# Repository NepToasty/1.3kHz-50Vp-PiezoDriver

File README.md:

# 1.3kHz-50Vp-PiezoDriver
1.3kHz 50Vp PiezoDriver

## Safety Warning and Disclaimer

This project is an experimental open-source hardware design. It can generate and/or expose voltages greater than 30 VAC, including potentially hazardous voltages. Contact with energized parts may cause electric shock, burns, equipment damage, fire, injury, or death.

This design is provided for informational, educational, and experimental use only. It is not a certified product, not safety-approved, and not intended for use in medical, life-support, safety-critical, automotive, industrial control, or other applications where failure could cause injury, death, property damage, or regulatory non-compliance.

Anyone who builds, modifies, tests, powers, or uses this design does so entirely at their own risk. The user is solely responsible for verifying the design, selecting suitable components, following applicable electrical safety practices, using appropriate insulation, fusing, enclosures, creepage/clearance distances, personal protective equipment, and complying with all applicable laws, standards, and regulations.

The authors, contributors, and copyright holders make no warranties or guarantees of any kind, express or implied, including but not limited to correctness, safety, fitness for a particular purpose, reliability, regulatory compliance, or suitability for any application.

To the fullest extent permitted by law, the authors, contributors, and copyright holders shall not be liable for any claim, damage, injury, loss, expense, or other liability arising from or related to the use, misuse, construction, modification, testing, or distribution of this project or any device based on it.

Do not build or operate this project unless you understand the risks of working with hazardous voltages.

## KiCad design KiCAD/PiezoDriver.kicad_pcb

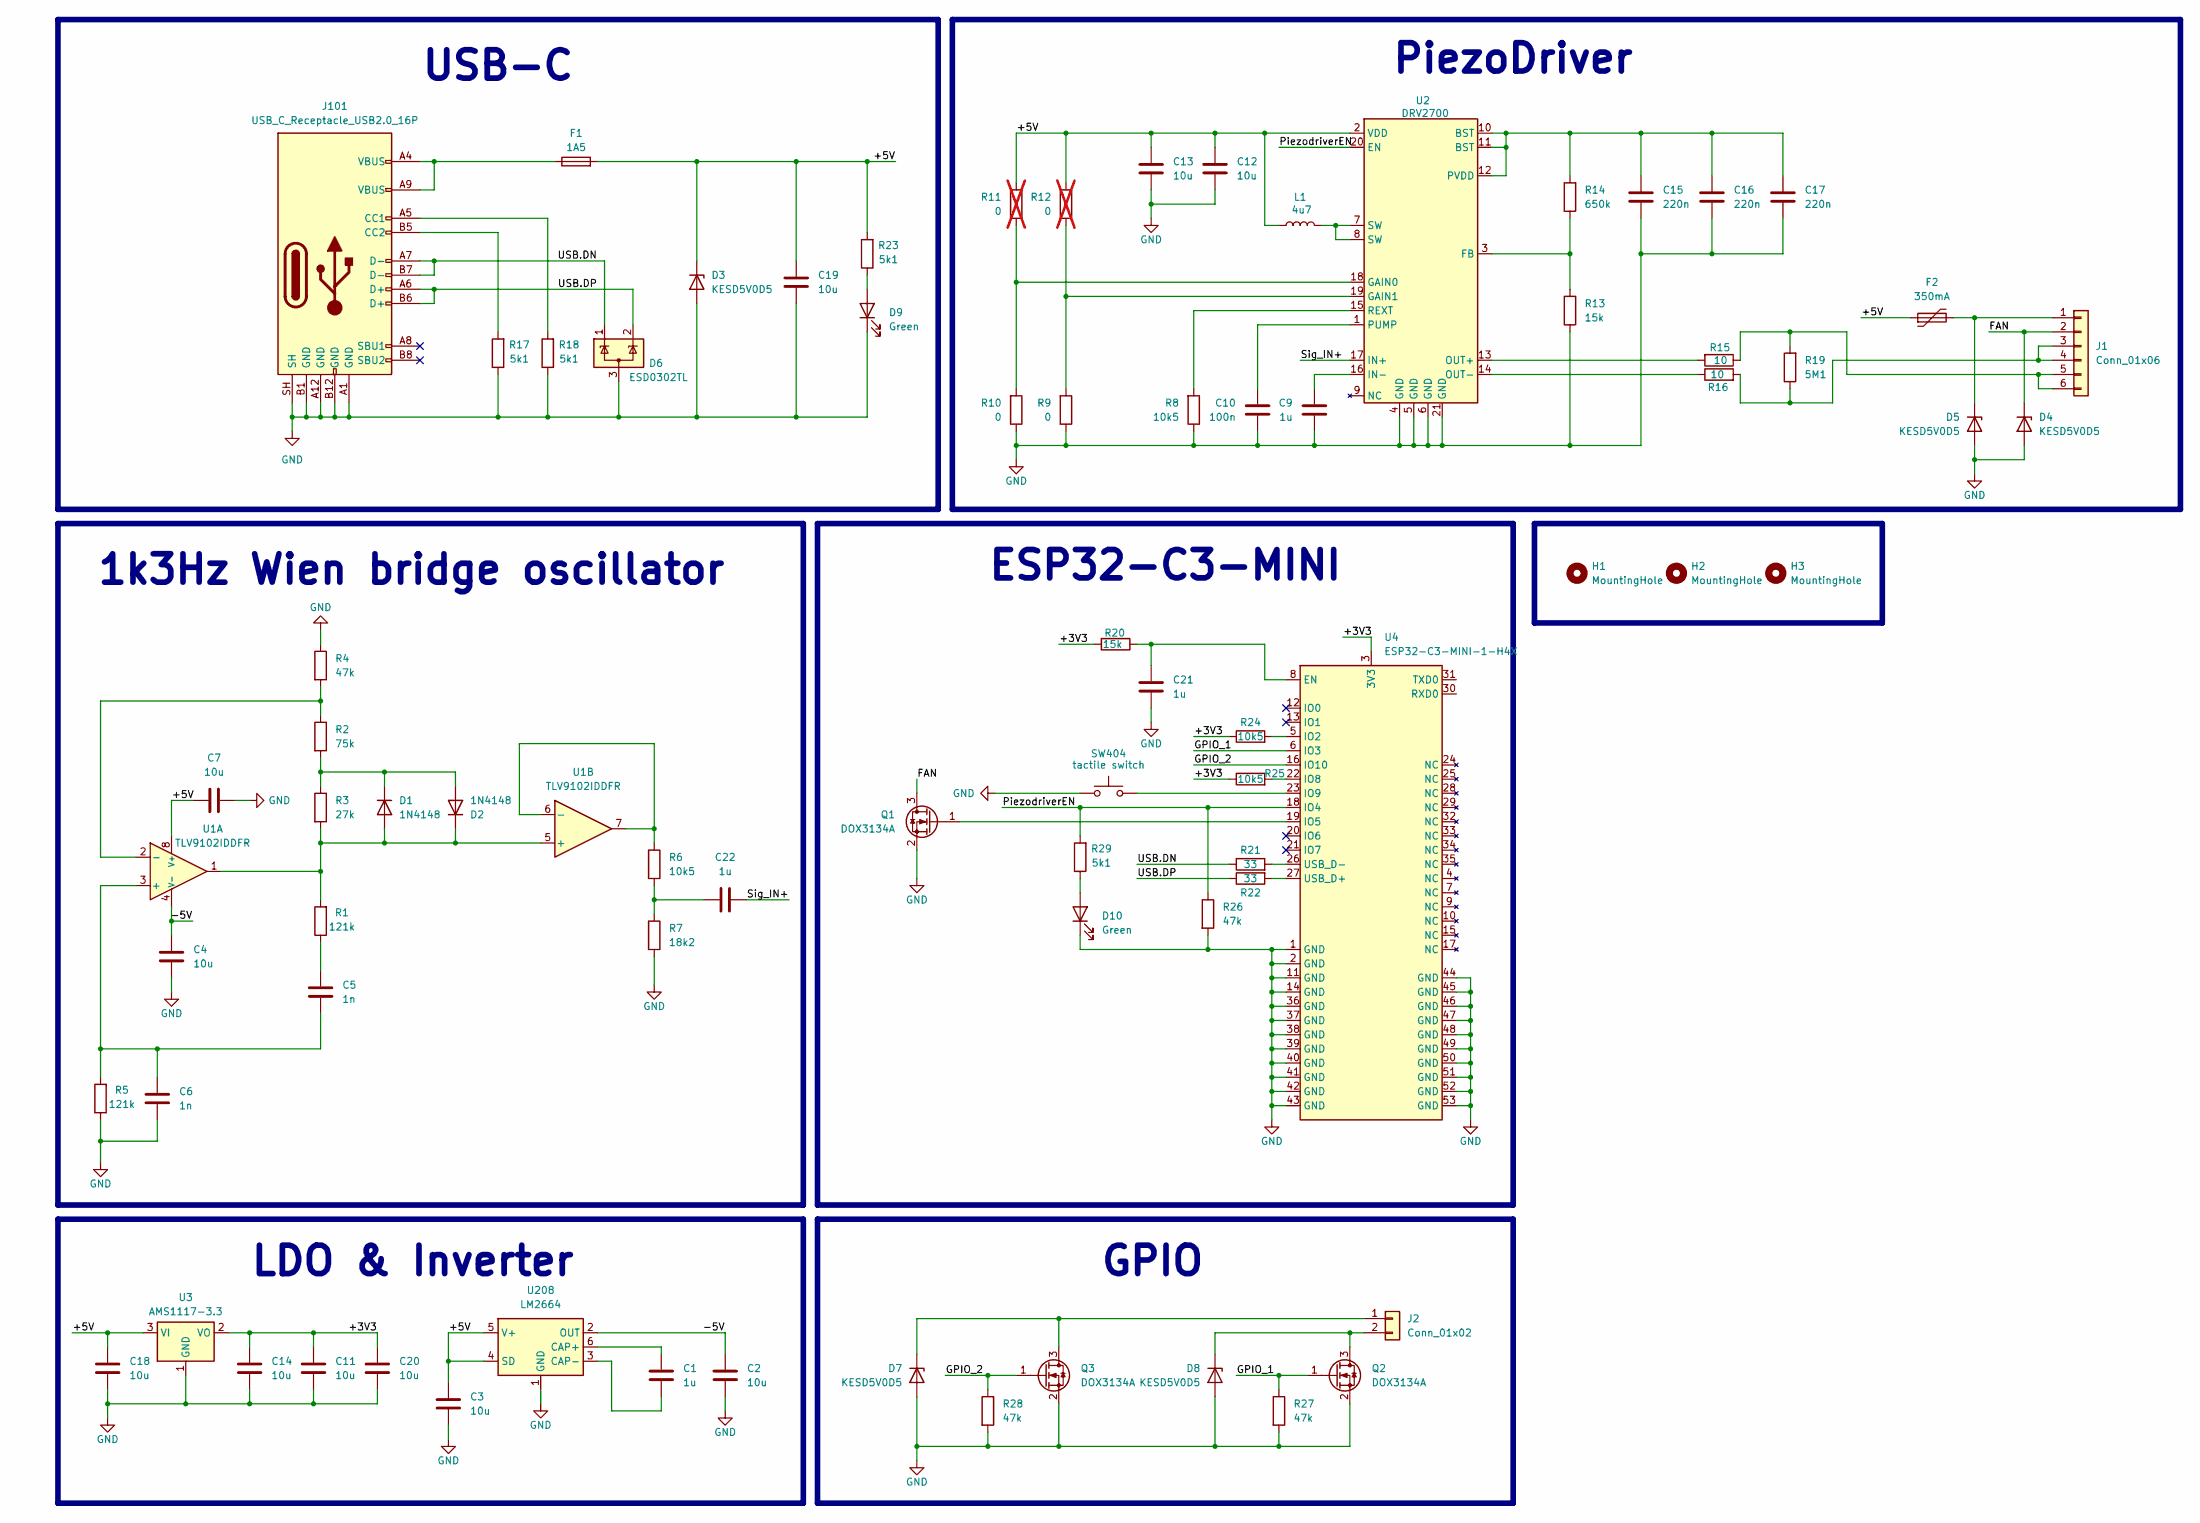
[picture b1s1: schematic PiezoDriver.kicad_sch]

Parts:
C1, C9, C21, C22: 1u; C_0603_1608Metric; LCSC C5199872
C2, C3, C4, C7, C11, C12, C13, C14, C18, C19, C20: 10u; C_0603_1608Metric; LCSC C6119842
C5, C6: 1n; C_0402_1005Metric; LCSC C76947
C10: 100n; C_0402_1005Metric; LCSC C77020
C15, C16, C17: 220n; C_1206_3216Metric; LCSC C880778
D1, D2: 1N4148; D_SOD-323; LCSC C60580
D3, D4, D5, D7, D8: KESD5V0D5; D_SOD-523; LCSC C2892517
D6: ESD0302TL; SOT-23; LCSC C502588
D9: Green; LED_0603_1608Metric; LCSC C52675989
D10: Green; LED_0603_1608Metric; LCSC C51933298
F1: 1A5; Fuse_0603_1608Metric; LCSC C52988544
F2: 350mA; Fuse_0603_1608Metric; LCSC C7501938
H1, H2, H3: MountingHole; MountingHole_2.2mm_M2_DIN965
J1: Conn_01x06; PinHeader_1x06_P2.54mm_Vertical
J2: Conn_01x02; PinHeader_1x02_P2.54mm_Vertical
J101: USB_C_Receptacle_USB2.0_16P; USB_C_Receptacle_G-Switch_GT-USB-7010ASV; MPN HYCW638-USBC16-650B; LCSC C53185061
L1: 4u7; L_Vishay_IFSC-1515AH_4x4x1.8mm; LCSC C92961
Q1, Q2, Q3: DOX3134A; SOT-323_SC-70; LCSC C54349756
R1, R5: 121k; R_0402_1005Metric; LCSC C11693
R2: 75k; R_0402_1005Metric; LCSC C2982949
R3: 27k; R_0402_1005Metric; LCSC C25551
R4, R26, R27, R28: 47k; R_0402_1005Metric; LCSC C2759770
R6, R8, R24, R25: 10k5; R_0402_1005Metric; LCSC C171695
R7: 18k2; R_0402_1005Metric; LCSC C25859
R9, R10: 0; R_0402_1005Metric; LCSC C163804
R11, R12: 0; R_0402_1005Metric; LCSC C163804; not fitted
R13, R20: 15k; R_0402_1005Metric; LCSC C25539
R14: 650k; R_0805_2012Metric; LCSC C137500
R15, R16: 10; R_0805_2012Metric; LCSC C25278
R17, R18, R23, R29: 5k1; R_0402_1005Metric; LCSC C25905
R19: 5M1; R_0805_2012Metric; LCSC C26118
R21, R22: 33; R_0402_1005Metric; LCSC C168263
SW404: tactile switch; SW_Push_SPST_NO_Alps_SKRK; MPN B3U-1000P; LCSC Part C720477
U1: TLV9102IDDFR; SOT-23-8; LCSC C4366877
U2: DRV2700; Texas_RGP0020D_VQFN-20-1EP_4x4mm_P0.5mm_EP2.7x2.7mm; LCSC C2150456
U3: AMS1117-3.3; SOT-89-3; LCSC C50313802
U4: ESP32-C3-MINI-1-H4X; ESP32-C6-MINI-1; LCSC C41349510
U208: LM2664; SOT-23-6; MPN LM2664M6X/NOPB; Mouser Nr. 926-LM2664M6X/NOPB

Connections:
/+3V3: C11.1, C14.1, C20.1, R20.2, R24.1, R25.1, U3.2 (VO), U4.3 (3V3)
/+5V: C3.1, C7.1, C12.2, C13.2, C18.1, C19.2, D3.1 (K), F1.2, F2.1, L1.1, R11.2, R12.2, R23.2, U1.8 (V+), U2.2 (VDD), U3.3 (VI), U208.4 (SD), U208.5 (V+)
/-5V: C2.1, C4.1, U1.4 (V-), U208.2 (OUT)
/FAN: D4.1 (K), J1.2, Q1.3 (D)
/GPIO_1: Q2.1 (G), R27.1, U4.6 (IO3)
/GPIO_2: Q3.1 (G), R28.1, U4.16 (IO10)
/PiezodriverEN: R26.1, R29.2, U2.20 (EN), U4.18 (IO4)
/Sig_IN+: C22.2, U2.17 (IN+)
/USB.DN: D6.1 (K), J101.A7 (D-), J101.B7 (D-), R21.1
/USB.DP: D6.2 (K), J101.A6 (D+), J101.B6 (D+), R22.1
GND: C2.2, C3.2, C4.2, C6.2, C7.2, C9.1, C10.2, C11.2, C12.1, C13.1, C14.2, C15.1, C16.1, C17.1, C18.2, C19.1, C20.2, C21.2, D3.2 (A), D4.2 (A), D5.2 (A), D6.3 (A), D7.2 (A), D8.2 (A), D9.1 (K), D10.1 (K), J101.A1 (GND), J101.A12 (GND), J101.B1 (GND), J101.B12 (GND), J101.SH, Q1.2 (S), Q2.2 (S), Q3.2 (S), R4.1, R5.1, R7.2, R8.1, R9.1, R10.1, R13.1, R17.1, R18.1, R26.2, R27.2, R28.2, SW404.1, U2.4 (GND), U2.5 (GND), U2.6 (GND), U2.21 (GND), U3.1 (GND), U4.1 (GND), U4.2 (GND), U4.11 (GND), U4.14 (GND), U4.36 (GND), U4.37 (GND), U4.38 (GND), U4.39 (GND), U4.40 (GND), U4.41 (GND), U4.42 (GND), U4.43 (GND), U4.44 (GND), U4.45 (GND), U4.46 (GND), U4.47 (GND), U4.48 (GND), U4.49 (GND), U4.50 (GND), U4.51 (GND), U4.52 (GND), U4.53 (GND), U208.1 (GND)
unnamed: C5.1, R1.1
unnamed: C22.1, R6.2, R7.1
unnamed: D1.2 (A), D2.1 (K), R1.2, R3.2, U1.1, U1.5 (+)
unnamed: D1.1 (K), D2.2 (A), R2.2, R3.1
unnamed: D5.1 (K), F2.2, J1.1
unnamed: D7.1 (K), J2.1, Q3.3 (D)
unnamed: D8.1 (K), J2.2, Q2.3 (D)
unnamed: D9.2 (A), R23.1
unnamed: D10.2 (A), R29.1
unnamed: F1.1, J101.A4 (VBUS), J101.A9 (VBUS), J101.B4 (VBUS), J101.B9 (VBUS)
unnamed: J1.3, J1.4, R16.2, R19.1
unnamed: J1.5, J1.6, R15.1, R19.2
unnamed: J101.A5 (CC1), R18.2
unnamed: J101.B5 (CC2), R17.2
unnamed: L1.2, U2.7 (SW), U2.8 (SW)
unnamed: Q1.1 (G), U4.19 (IO5)
unnamed: C5.2, C6.1, R5.2, U1.3 (+)
unnamed: R2.1, R4.2, U1.2 (-)
unnamed: R6.1, U1.6 (-), U1.7
unnamed: R13.2, R14.1, U2.3 (FB)
unnamed: R10.2, R11.1, U2.18 (GAIN0)
unnamed: R9.2, R12.1, U2.19 (GAIN1)
unnamed: C9.2, U2.16 (IN-)
unnamed: R15.2, U2.13 (OUT+)
unnamed: R16.1, U2.14 (OUT-)
unnamed: C10.1, U2.1 (PUMP)
unnamed: C15.2, C16.2, C17.2, R14.2, U2.10 (BST), U2.11 (BST), U2.12 (PVDD)
unnamed: R8.2, U2.15 (REXT)
unnamed: C21.1, R20.1, U4.8 (EN)
unnamed: R24.2, U4.5 (IO2)
unnamed: R25.2, U4.22 (IO8)
unnamed: SW404.2, U4.23 (IO9)
unnamed: R22.2, U4.27 (USB_D+)
unnamed: R21.2, U4.26 (USB_D-)
unnamed: C1.1, U208.6 (CAP+)
unnamed: C1.2, U208.3 (CAP-)

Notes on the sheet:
USB-C
LDO & Inverter
PiezoDriver
ESP32-C3-MINI
1k3Hz Wien bridge oscillator
GPIO

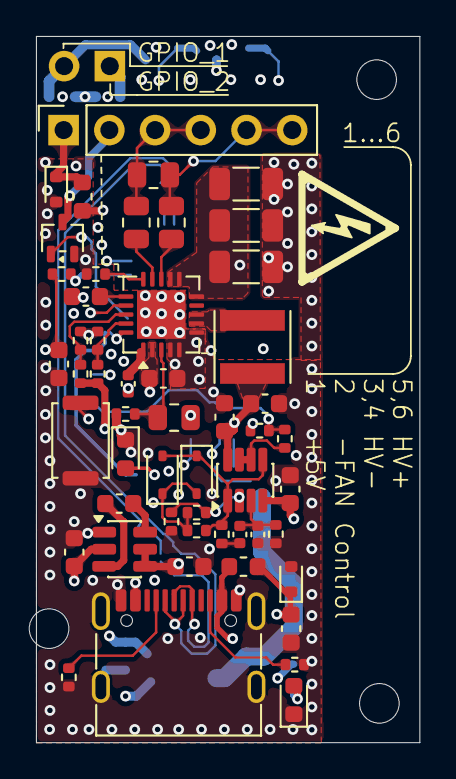
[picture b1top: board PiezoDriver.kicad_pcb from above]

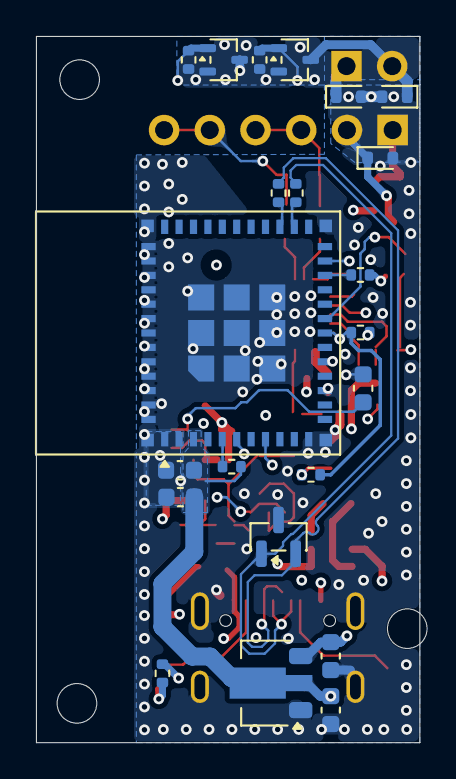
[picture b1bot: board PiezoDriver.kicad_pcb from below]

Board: 6 copper layers, 21.3 x 39.2 mm, 78 parts (22 on the bottom side), 47 nets.

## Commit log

2026-05-18 Added Project Files
